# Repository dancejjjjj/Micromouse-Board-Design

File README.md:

# Micromouse Hardware Design (KiCad)

Hardware schematics and design files for an autonomous Micromouse robot based on the **ESP32-S3 SuperMini**.

---

> ⚠️ **IMPORTANT NOTICE:**  
> The physical hardware of this robot is built entirely on a **Prototype Board (Perfboard/Dot board)** using manual point-to-point soldering.  
> The included **PCB layout file (`.kicad_pcb`) is provided for reference only** (visualizing routing logic and footprint planning) and **has NOT been tested or validated for direct PCB manufacturing**. Please refer to the **Schematic (`.kicad_sch`)** for wiring connections when assembling on a proto-board or designing your custom PCB.

---

## 🧩 Bill of Materials (Key Components)

Google sheet link here:
https://docs.google.com/spreadsheets/d/1piouLKvGbAHOj3b3Lox_jSpBq9OYytLLw8UId9fDQRM/edit?usp=sharing

---

## 📁 Repository Structure

```text
.
├── pcb/
│   ├── micromouse.kicad_pro     # KiCad Project File
│   ├── micromouse.kicad_sch     # Full Circuit Schematic (Primary reference)
│   └── micromouse.kicad_pcb     # Reference PCB Layout (Do NOT fabricate directly)
|   
├── BOM.csv
└── README.md
```
## View it 
https://kicanvas.org/?repo=https%3A%2F%2Fgithub.com%2Fdancejjjjj%2FMicromouse-Board-Design%2Ftree%2Fmain%2Fpcb

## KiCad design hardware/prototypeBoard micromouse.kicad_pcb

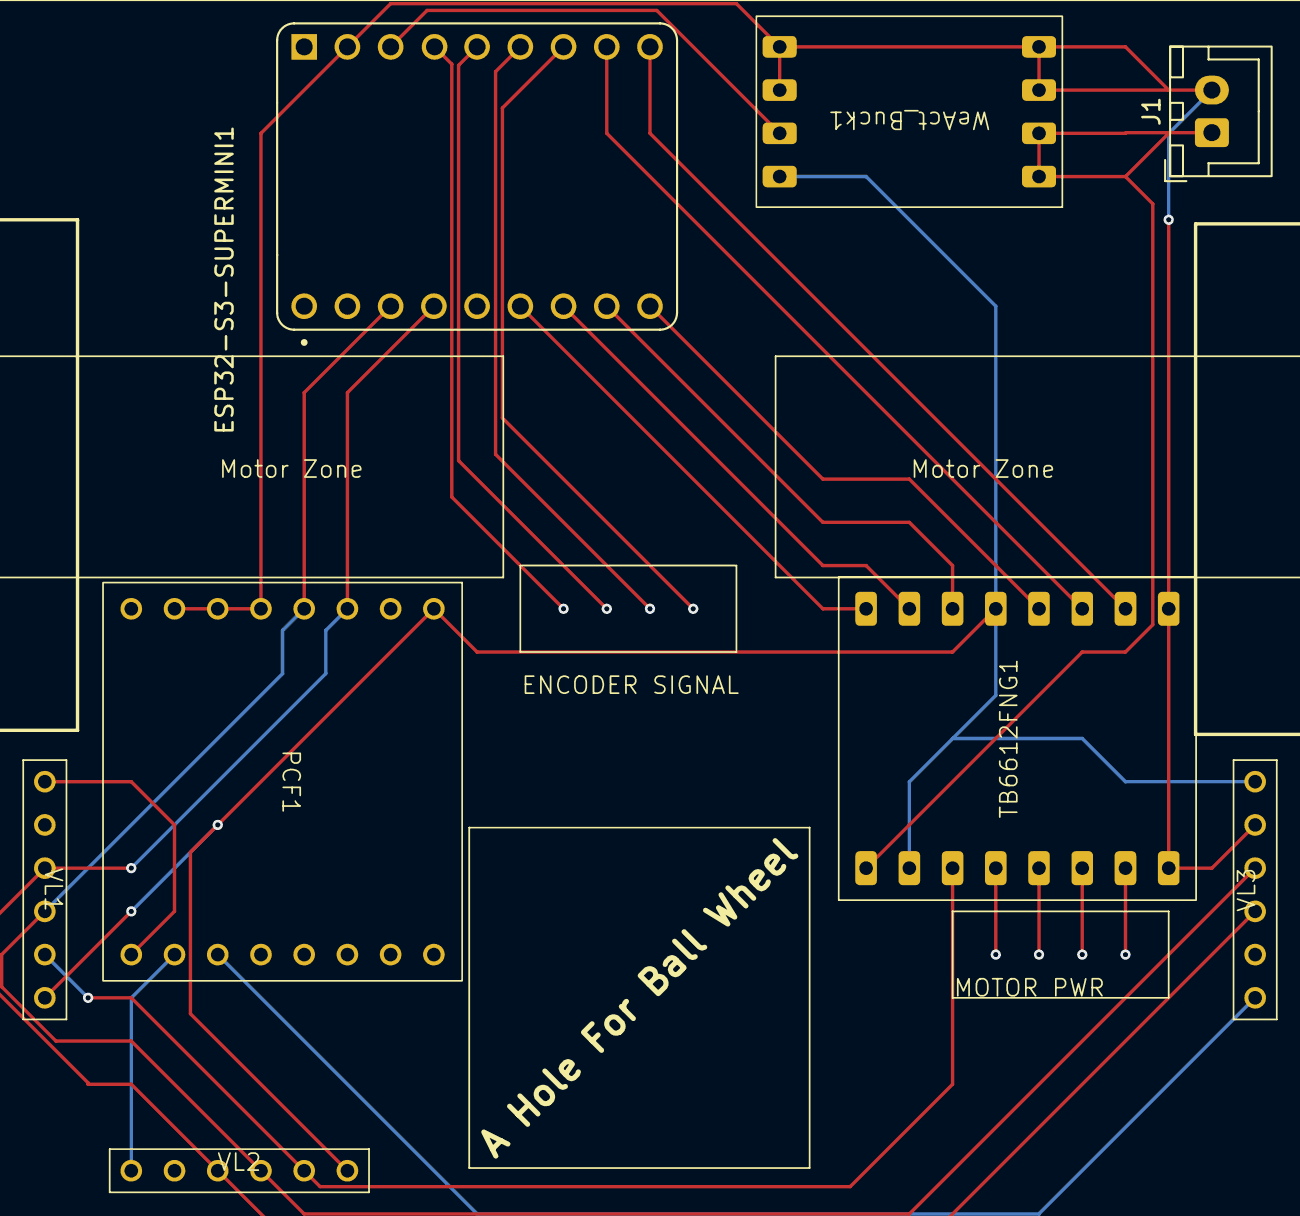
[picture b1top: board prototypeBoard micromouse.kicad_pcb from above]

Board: 2 copper layers, 8 parts (0 on the bottom side), 14 nets.

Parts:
ESP32-S3-SUPERMINI1: ESP32-S3-SuperMini
J1: Conn_01x02_Pin; JST_XH_B2B-XH-A_1x02_P2.50mm_Vertical
PCF1: MCU8574-PCF8574T
TB6612FNG1: TB6612FNG
VL1, VL2, VL3: TOF050C_VL6180_PinOnly
WeAct_Buck1: WeAct

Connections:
+3.3V: ESP32-S3-SUPERMINI1.3V3, PCF1.VCC, TB6612FNG1.STBY, TB6612FNG1.VCC, VL1.VCC, VL2.VCC, VL3.VCC, WeAct_Buck1.VOUT
+7.5V: J1.1, TB6612FNG1.VM, WeAct_Buck1.VCC
GND: ESP32-S3-SUPERMINI1.GND, J1.2, PCF1.A0, PCF1.A1, PCF1.A2, PCF1.GND, TB6612FNG1.GND, VL1.GND, VL2.GND, VL3.GND, WeAct_Buck1.GND
unnamed: ESP32-S3-SUPERMINI1.1, PCF1.SDA, VL1.SDA, VL2.SDA, VL3.SDA
unnamed: ESP32-S3-SUPERMINI1.2, PCF1.SCL, VL1.SCL, VL2.SCL, VL3.SCL
unnamed: ESP32-S3-SUPERMINI1.4, TB6612FNG1.PWMA
unnamed: ESP32-S3-SUPERMINI1.5, TB6612FNG1.AIN2
unnamed: ESP32-S3-SUPERMINI1.6, TB6612FNG1.AIN1
unnamed: ESP32-S3-SUPERMINI1.7, TB6612FNG1.BIN1
unnamed: ESP32-S3-SUPERMINI1.8, TB6612FNG1.PWMB
unnamed: ESP32-S3-SUPERMINI1.9, TB6612FNG1.BIN2
unnamed: PCF1.0, VL1.XSHUT
unnamed: PCF1.1, VL2.XSHUT
unnamed: PCF1.2, VL3.XSHUT

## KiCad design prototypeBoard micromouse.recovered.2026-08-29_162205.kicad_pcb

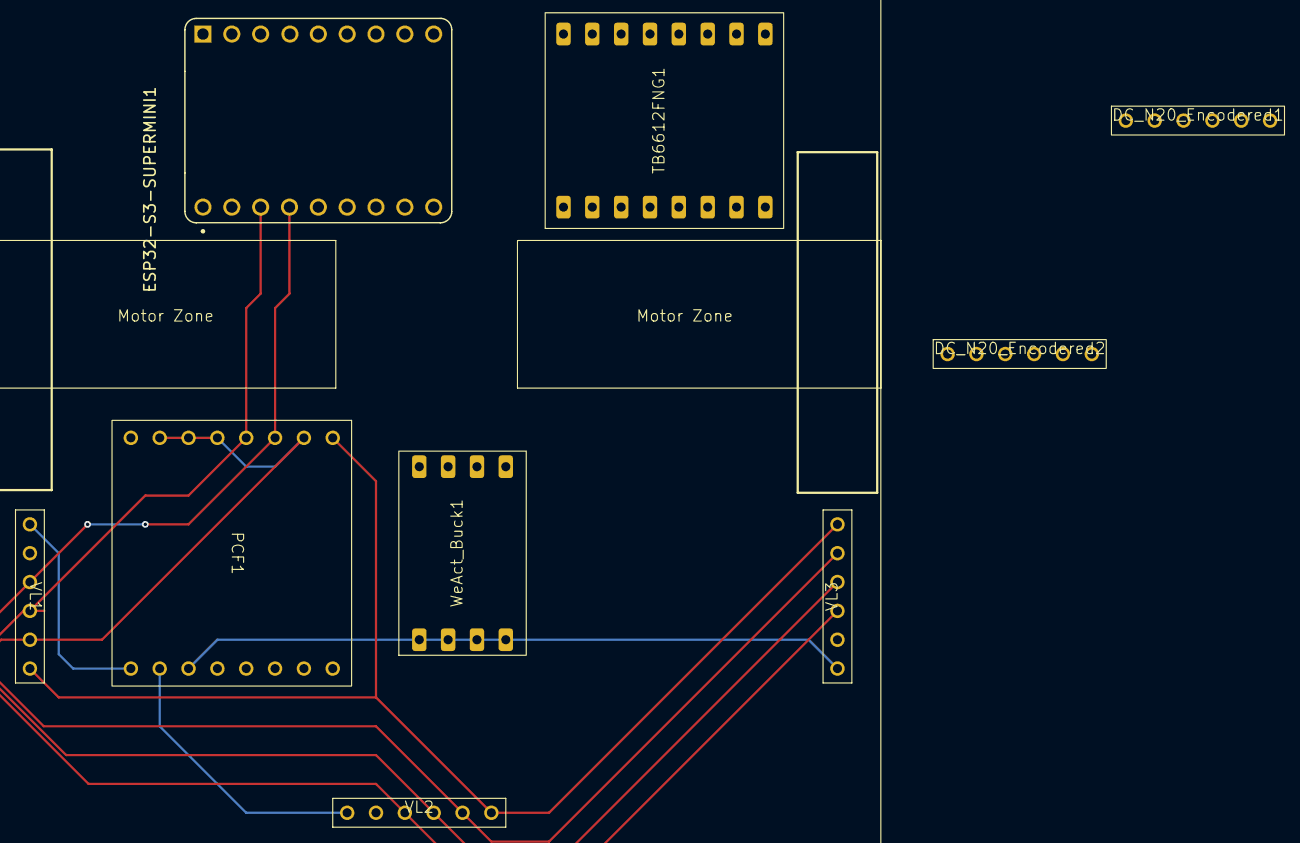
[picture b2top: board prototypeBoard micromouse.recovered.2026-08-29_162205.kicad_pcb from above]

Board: 2 copper layers, 9 parts (0 on the bottom side), 22 nets.

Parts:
DC_N20_Encodered1, DC_N20_Encodered2: N20_Encodered_PinOnly
ESP32-S3-SUPERMINI1: ESP32-S3-SuperMini
PCF1: MCU8574-PCF8574T
TB6612FNG1: TB6612FNG
VL1, VL2, VL3: TOF050C_VL6180_PinOnly
WeAct_Buck1: WeAct

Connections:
+7.5V: TB6612FNG1.VM, WeAct_Buck1.VCC
GND: DC_N20_Encodered1.GND, DC_N20_Encodered2.GND, ESP32-S3-SUPERMINI1.GND, PCF1.A0, PCF1.A1, PCF1.A2, PCF1.GND, TB6612FNG1.GND, VL1.GND, VL2.GND, VL3.GND, WeAct_Buck1.GND
unnamed: DC_N20_Encodered1.E1, ESP32-S3-SUPERMINI1.12
unnamed: DC_N20_Encodered1.E2, ESP32-S3-SUPERMINI1.13
unnamed: DC_N20_Encodered1.M1, TB6612FNG1.B1
unnamed: DC_N20_Encodered1.M2, TB6612FNG1.B2
unnamed: DC_N20_Encodered1.VCC, DC_N20_Encodered2.VCC, ESP32-S3-SUPERMINI1.3V3, PCF1.VCC, TB6612FNG1.STBY, TB6612FNG1.VCC, VL1.VCC, VL2.VCC, VL3.VCC, WeAct_Buck1.VOUT
unnamed: DC_N20_Encodered2.E1, ESP32-S3-SUPERMINI1.10
unnamed: DC_N20_Encodered2.E2, ESP32-S3-SUPERMINI1.11
unnamed: DC_N20_Encodered2.M1, TB6612FNG1.A1
unnamed: DC_N20_Encodered2.M2, TB6612FNG1.A2
unnamed: ESP32-S3-SUPERMINI1.1, PCF1.SDA, VL1.SDA, VL2.SDA, VL3.SDA
unnamed: ESP32-S3-SUPERMINI1.2, PCF1.SCL, VL1.SCL, VL2.SCL, VL3.SCL
unnamed: ESP32-S3-SUPERMINI1.4, TB6612FNG1.AIN2
unnamed: ESP32-S3-SUPERMINI1.5, TB6612FNG1.AIN1
unnamed: ESP32-S3-SUPERMINI1.6, TB6612FNG1.BIN1
unnamed: ESP32-S3-SUPERMINI1.7, TB6612FNG1.BIN2
unnamed: ESP32-S3-SUPERMINI1.8, TB6612FNG1.PWMA
unnamed: ESP32-S3-SUPERMINI1.9, TB6612FNG1.PWMB
unnamed: PCF1.0, VL1.XSHUT
unnamed: PCF1.1, VL2.XSHUT
unnamed: PCF1.2, VL3.XSHUT
